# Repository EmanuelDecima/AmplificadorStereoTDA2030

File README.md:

# Amplificador Estéreo TDA2030  

## Descripción  
Este proyecto es un **amplificador estéreo basado en el integrado TDA2030**, diseñado para ofrecer una solución compacta y de buen desempeño para aplicaciones de audio Hi-Fi, educación y prototipado. El diseño incluye PCB, esquemático, lista de materiales y archivos listos para fabricación.

## 🔧 Características principales  
- Dos canales de audio (izquierda y derecha) utilizando TDA2030 en configuración típica.  
- Diseño de PCB simple faz, con huella optimizada para montaje a través de orificio (THT).
- Fuente de alimentación simple (recomendado 12VDC).
- Listado de materiales (BOM) incluido en formatos PDF y XLS.  
- Archivos de fabricación (Gerbers, ficheros KiCad) incluidos.  
- Ideal para amplificación de señal de línea, sistemas de escritorio, audio doméstico o proyecto educativo.

## 🖼️ Esquema y PCB  
*(Insertar imágenes aquí para visualización rápida)*  

## ⚙️ Documentación técnica  
### Arquitectura general  
El amplificador emplea dos unidades TDA2030, una por canal, en configuración con decouplado de alimentación, filtro de entrada y componentes de realimentación para ganancia moderada (~20–30x).  
Se dispone de conectores de entrada de audio de línea, potenciometro/selector de ganancia, y salidas de altavoz de 4 Ω-8 Ω.

### Consideraciones de diseño  
- Se recomienda usar disipadores térmicos en los TDA2030 si la potencia exigida es alta.
- La entrada de audio debe ser preamplificada anteriormente hasta el voltaje de linea 1Vrms.

## 🧰 Requisitos y compatibilidad  
### Requisitos  
- Fuente de alimentación de 12V-DC.
- Altavoces de impedancia 4Ω o 8Ω.  
- Señal de entrada de nivel de línea 1Vrms.  
- Habilidades básicas de soldadura para montaje THT.

### Compatibilidad  
Este diseño está pensado para montaje en ambiente “hobby/prototipo” y también escalable para proyectos de audio doméstico o educativo.

## 💻 Ejemplo de uso  
1. Montar la PCB según el archivo de montaje y la lista de materiales.  
2. Conectar la alimentación y verificar tensiones (sin señal).  
3. Conectar entrada y altavoces.  
4. Aplicar señal de audio de línea, ajustar volumen, y comprobar ganancia, distorsión y estabilidad.  
5. Ajustar según necesidades (por ejemplo añadir filtro de paso bajo, control de volumen, etc).

## 👤 Autor  
Diseñado por Emanuel Décima  
📅 Fecha de última actualización: Noviembre 2025  
📧 Contacto: emanueldecima3@gmail.com

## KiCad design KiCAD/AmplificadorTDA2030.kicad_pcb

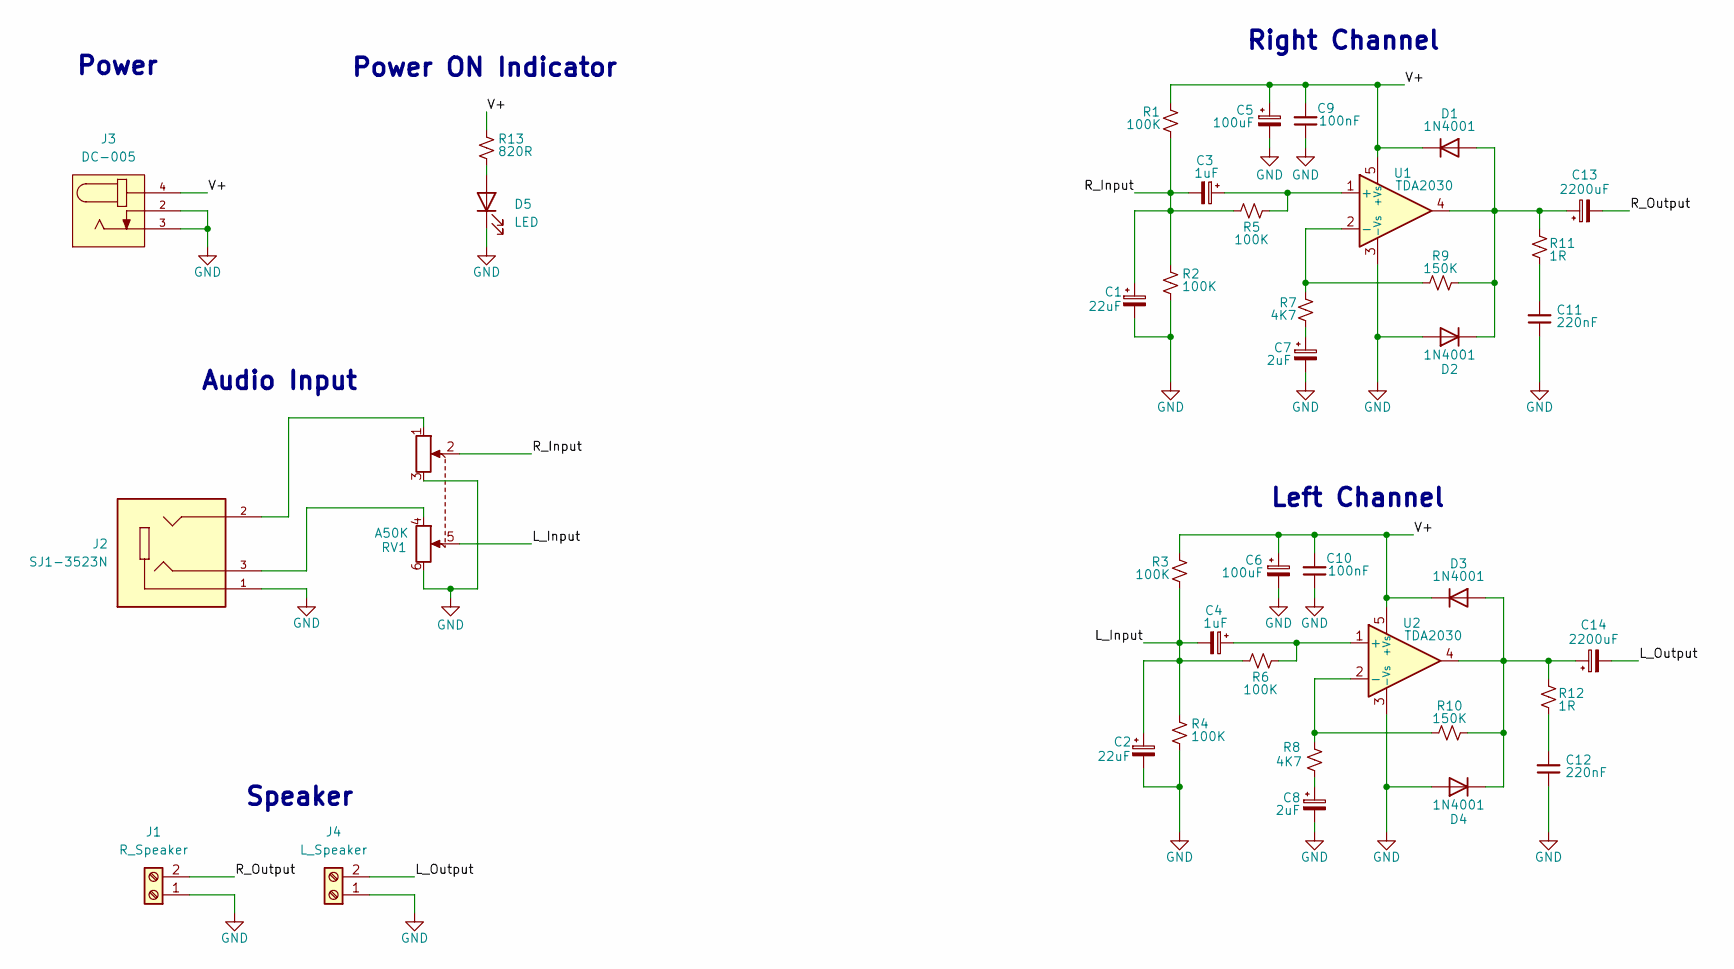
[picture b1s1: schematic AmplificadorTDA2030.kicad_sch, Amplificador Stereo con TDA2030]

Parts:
C1, C2: 22uF; CP_Radial_D6.3mm_P2.50mm
C3, C4: 1uF; CP_Radial_D4.0mm_P2.00mm
C5, C6: 100uF; CP_Radial_D6.3mm_P2.50mm
C7, C8: 2uF; CP_Radial_D4.0mm_P2.00mm
C9, C10: 100nF; C_Disc_D3.0mm_W2.0mm_P2.50mm
C11, C12: 220nF; C_Disc_D3.0mm_W2.0mm_P2.50mm
C13, C14: 2200uF; CP_Radial_D16.0mm_P7.50mm
D1, D2, D3, D4: 1N4001; D_DO-41_SOD81_P10.16mm_Horizontal
D5: LED; LED_D5.0mm
J1: R_Speaker; TerminalBlock_Phoenix_MKDS-1,5-2-5.08_1x02_P5.08mm_Horizont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
J2: SJ1-3523N; CUI_SJ1-3523N; PARTREV 1.05
J3: DC-005; NINIGI_DC-005
J4: L_Speaker; TerminalBlock_Phoenix_MKDS-1,5-2-5.08_1x02_P5.08mm_Horizont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
R1, R3: 100K; R_Axial_DIN0204_L3.6mm_D1.6mm_P7.62mm_Horizontal
R2, R4, R5, R6: 100K; R_Axial_DIN0204_L3.6mm_D1.6mm_P5.08mm_Horizontal
R7, R8: 4K7; R_Axial_DIN0204_L3.6mm_D1.6mm_P7.62mm_Horizontal
R9, R10: 150K; R_Axial_DIN0204_L3.6mm_D1.6mm_P7.62mm_Horizontal
R11, R12: 1R; R_Axial_DIN0204_L3.6mm_D1.6mm_P7.62mm_Horizontal
R13: 820R; R_Axial_DIN0204_L3.6mm_D1.6mm_P7.62mm_Horizontal
RV1: A50K; Potentiometer_Alps_RK163_Dual_Horizontal
U1, U2: TDA2030; TO-220-5_P3.4x3.7mm_StaggerOdd_Lead3.8mm_Vertical

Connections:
/L_Input: C2.1, C4.2, R3.1, R4.2, R6.1, RV1.5
/L_Output: C14.2, J4.2
/R_Input: C1.1, C3.2, R1.1, R2.2, R5.1, RV1.2
/R_Output: C13.2, J1.2
/V+: C5.1, C6.1, C9.2, C10.2, D1.1 (K), D3.1 (K), J3.4, R1.2, R3.2, R13.2, U1.5 (+Vs), U2.5 (+Vs)
GND: C1.2, C2.2, C5.2, C6.2, C7.2, C8.2, C9.1, C10.1, C11.1, C12.1, D2.2 (A), D4.2 (A), D5.1 (K), J1.1, J2.1, J3.2, J3.3, J4.1, R2.1, R4.1, RV1.3, RV1.6, U1.3 (-Vs), U2.3 (-Vs)
unnamed: C7.1, R7.1
unnamed: C8.1, R8.1
unnamed: C11.2, R11.1
unnamed: C12.2, R12.1
unnamed: C13.1, D1.2 (A), D2.1 (K), R9.1, R11.2, U1.4
unnamed: C14.1, D3.2 (A), D4.1 (K), R10.1, R12.2, U2.4
unnamed: D5.2 (A), R13.1
unnamed: J2.2, RV1.1
unnamed: J2.3, RV1.4
unnamed: C3.1, R5.2, U1.1 (+)
unnamed: R7.2, R9.2, U1.2 (-)
unnamed: C4.1, R6.2, U2.1 (+)
unnamed: R8.2, R10.2, U2.2 (-)

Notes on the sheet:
Right Channel
Power ON Indicator
Power
Speaker
Left Channel
Audio Input

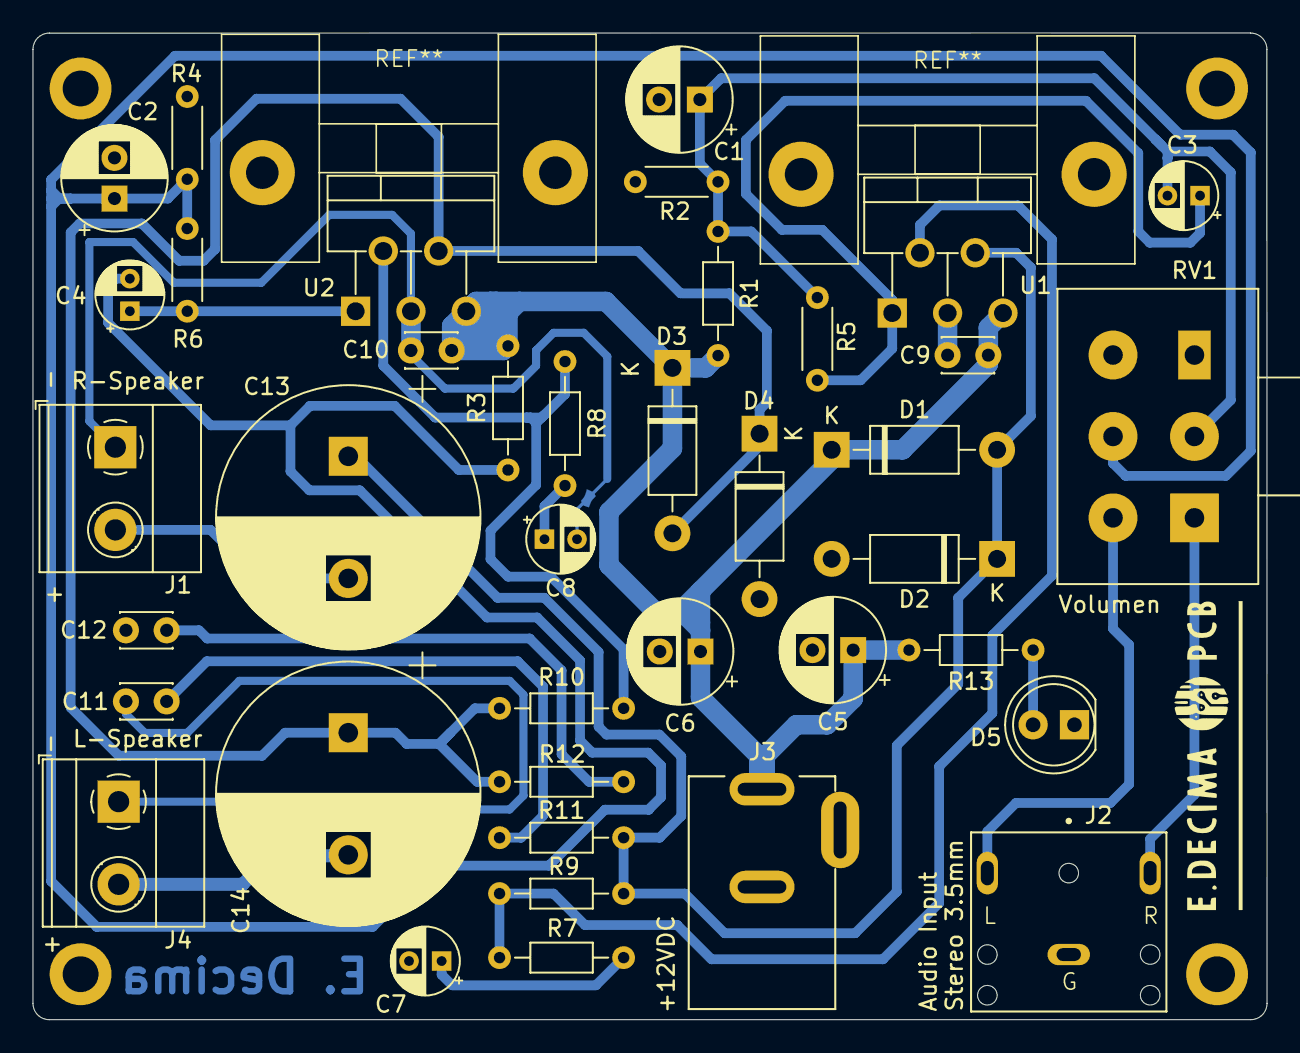
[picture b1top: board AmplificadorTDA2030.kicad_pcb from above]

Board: 2 copper layers, 75.8 x 60.6 mm, 39 parts (0 on the bottom side), 19 nets.

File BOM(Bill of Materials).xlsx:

Componente | Cant. | Precio Unitario | Subtotal
TDA2030 | 2 | 2631.7 | 5263.4
Conector DC-005 | 1 | 862.2 | 862.2
Conector Audio Stereo 3,5mm | 1 | 2914.57 | 2914.57
Bornera de 2 Entradas | 2 | 1301.75 | 2603.5
Led 5mm | 1 | 1490 | 1490
Potenciometro Doble A50K | 1 | 4023 | 4023
Resistencia 150K a 1/4W | 2 | 298 | 596
Resistencia 100K a 1/4W | 6 | 298 | 1788
Resistencia 4K7 a 1/4W | 2 | 298 | 596
Resistencia 820R a 1/4W | 1 | 298 | 298
Resistencia 1R a 1/4W | 2 | 298 | 596
Diodo 1N4001 | 4 | 166 | 664
Capacitor Electrolitico 2200uF/35V | 2 | 2974.15 | 5948.3
Capacitor Electrolitico 100uF/35V | 2 | 483.89 | 967.78
Capacitor Electrolitico 22uF/35V | 2 | 200 | 400
Capacitor Electrolitico 2,2uF/35V | 2 | 94.56 | 189.12
Capacitor Electrolitico 1uF/35V | 2 | 129 | 258
Capacitor Ceramico 100nF | 2 | 100 | 200
Capacitor Ceramico 220nF | 2 | 100 | 200
Total |  | 29857.869999999995

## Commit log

2024-09-25 Se agrega Esquematico y BOM
2024-09-25 Librerias de Simbolos,Footprints y Modelos 3D Agregados
2024-09-26 Footprints Asignados
2024-09-27 Ruteo de PCB correcto
2024-10-01 Se agrega LED y Disipadores
2024-10-01 Documentacion Actualizada
2024-11-20 Ruteo
2024-11-20 Acutalizacion de Doc
2024-11-24 Reorganizacion de Carpetas y Actualizacion de Documentacion
2024-11-24 Agrego diseño mecanico en AutoCAD
2025-03-05 Archivos Imprimibles
2025-07-19 Imagenes de PCB
2025-11-10 Add README for TDA2030 stereo amplifier project
    Added detailed project description, features, and usage instructions for the TDA2030 stereo amplifier.
2025-11-10 Fix image path for schematic in README
2025-11-10 Agrego imagen del esquematico
2025-11-10 Update schematic image from PDF to JPG format

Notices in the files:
README.md:
License: MIT
